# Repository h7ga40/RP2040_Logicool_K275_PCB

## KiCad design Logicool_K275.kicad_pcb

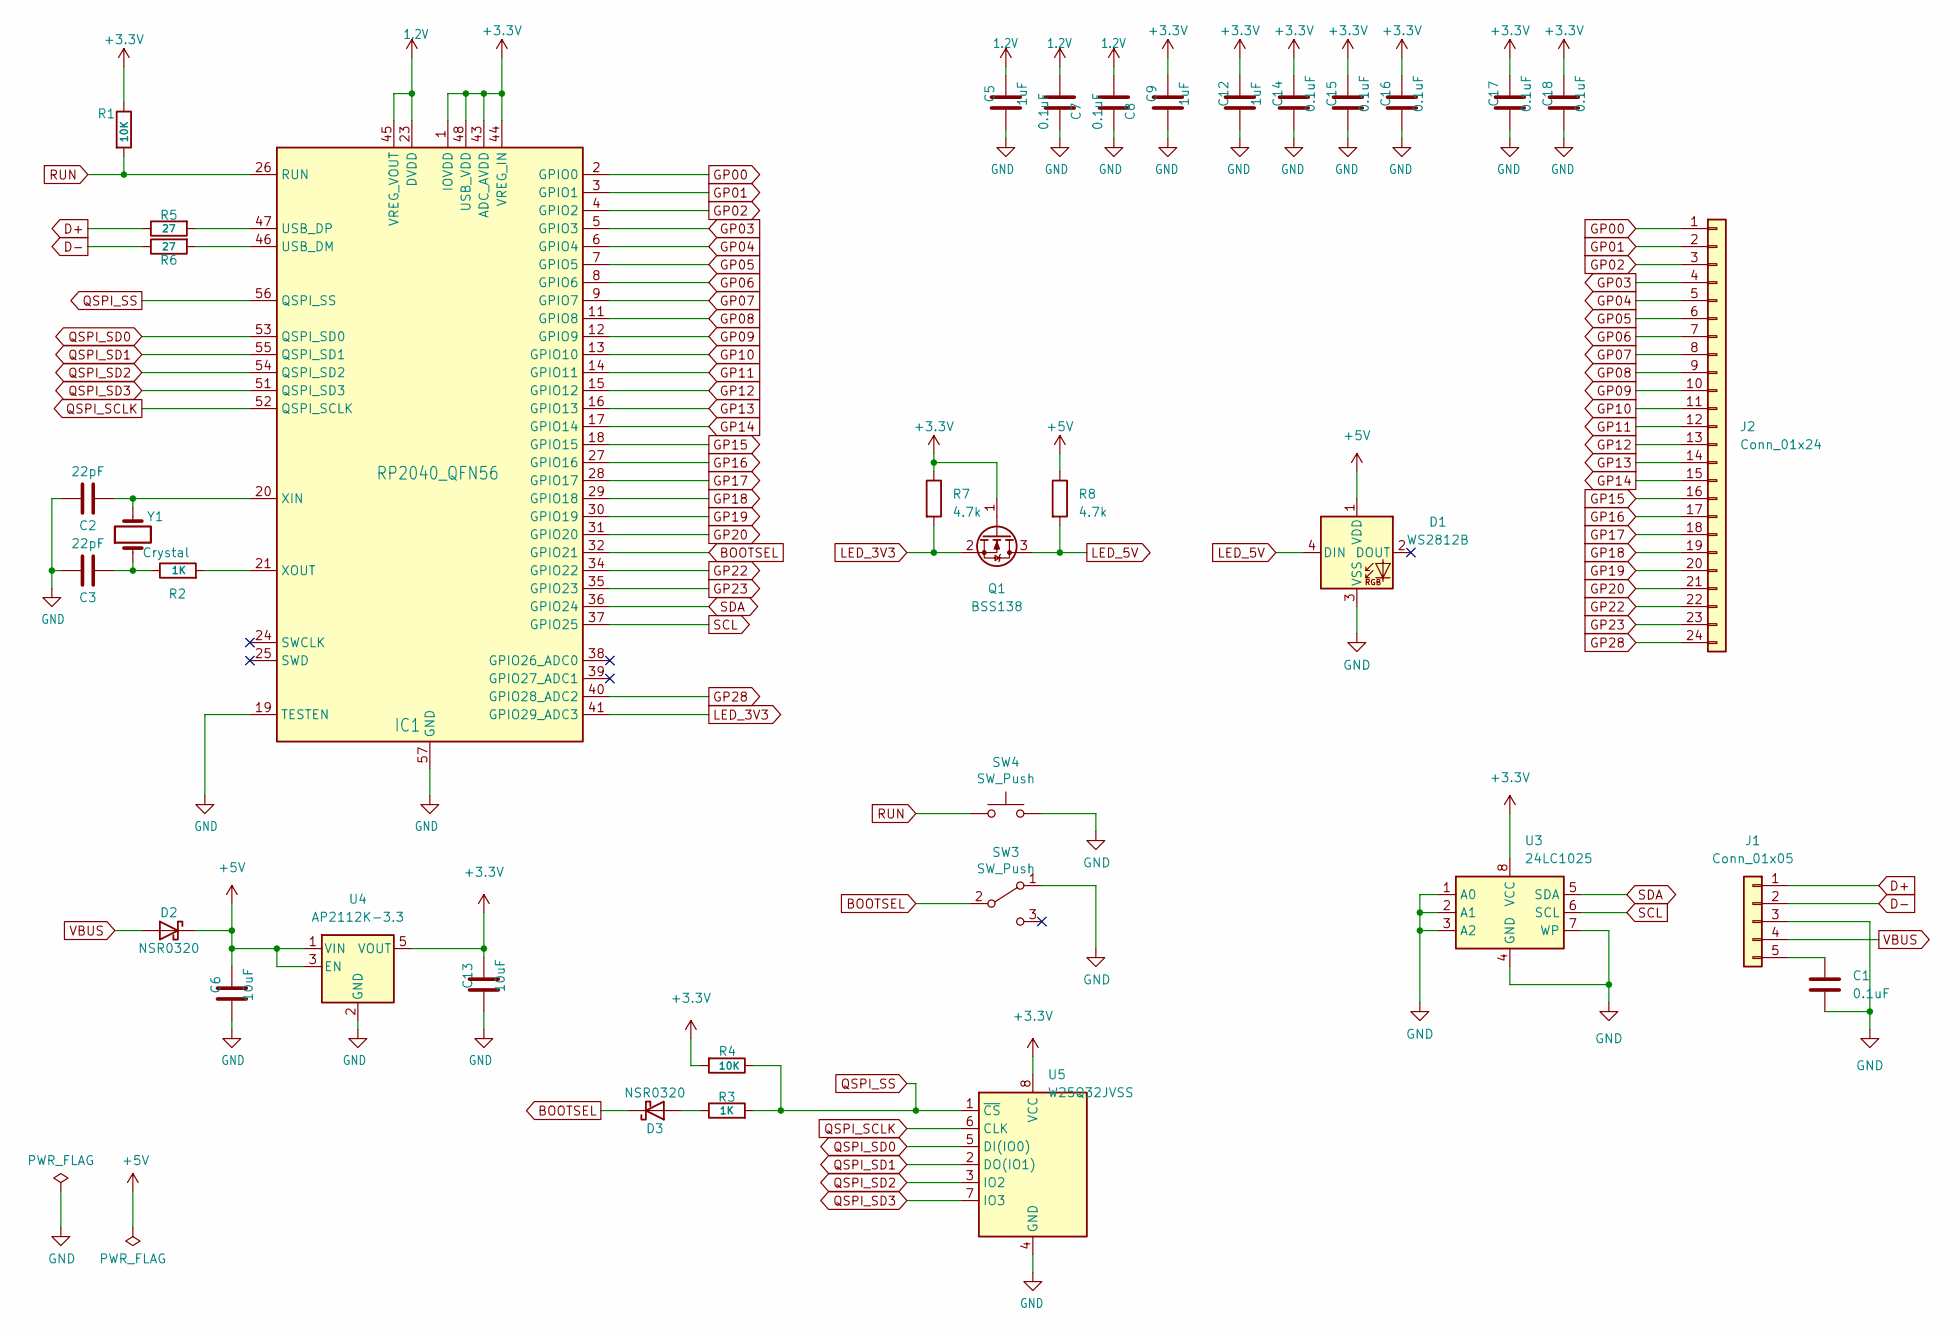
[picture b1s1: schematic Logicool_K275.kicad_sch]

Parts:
C1, C7, C8, C14, C15, C16, C17, C18: 0.1uF; C_0603_1608Metric_Pad1.08x0.95mm_HandSolder
C2, C3: 22pF; C_0603_1608Metric_Pad1.08x0.95mm_HandSolder
C5, C9, C12: 1uF; C_0603_1608Metric_Pad1.08x0.95mm_HandSolder
C6, C13: 10uF; C_0603_1608Metric_Pad1.08x0.95mm_HandSolder
D1: WS2812B; LED_WS2812B_PLCC4_5.0x5.0mm_P3.2mm
D2, D3: NSR0320; D_SOD-323_HandSoldering
IC1: RP2040_QFN56; QFN-56-1EP_7x7mm_P0.4mm_EP3.2x3.2mm
J1: Conn_01x05; PinHeader_1x05_P2.00mm_Vertical
J2: Conn_01x24; KeyMatrix
Q1: BSS138; SOT-23
R1, R4: 10K; R_0603_1608Metric_Pad0.98x0.95mm_HandSolder
R2, R3: 1K; R_0603_1608Metric_Pad0.98x0.95mm_HandSolder
R5, R6: 27; R_0603_1608Metric_Pad0.98x0.95mm_HandSolder
R7, R8: 4.7k; R_0603_1608Metric_Pad0.98x0.95mm_HandSolder
SW3: SW_Push; SW_SPDT_PCM12
SW4: SW_Push; SW_SPST_PTS810
U3: 24LC1025; SOP-8_3.9x4.9mm_P1.27mm
U4: AP2112K-3.3; SOT-23-5
U5: W25Q32JVSS; SOIC-8_5.23x5.23mm_P1.27mm
Y1: Crystal; Crystal_HC49-U_Vertical

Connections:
+1V2: C5.1, C7.2, C8.2, IC1.23 (DVDD), IC1.45 (VREG_VOUT), IC1.50 (DVDD)
+3.3V: C9.1, C12.1, C13.1, C14.1, C15.1, C16.1, C17.1, C18.1, IC1.1 (IOVDD), IC1.10 (IOVDD), IC1.22 (IOVDD), IC1.33 (IOVDD), IC1.42 (IOVDD), IC1.43 (ADC_AVDD), IC1.44 (VREG_IN), IC1.48 (USB_VDD), IC1.49 (IOVDD), Q1.1 (G), R1.1, R4.2, R7.1, U3.8 (VCC), U4.5 (VOUT), U5.8 (VCC)
+5V: C6.1, D1.1 (VDD), D2.1 (K), R8.1, U4.1 (VIN), U4.3 (EN)
BOOTSEL: D3.1 (K), IC1.32 (GPIO21), SW3.2 (B)
D+: J1.1, R5.1
D-: J1.2, R6.1
GND: C1.2, C2.1, C3.1, C5.2, C6.2, C7.1, C8.1, C9.2, C12.2, C13.2, C14.2, C15.2, C16.2, C17.2, C18.2, D1.3 (VSS), IC1.19 (TESTEN), IC1.57 (GND), J1.3, SW3.1 (A), SW4.2, U3.1 (A0), U3.2 (A1), U3.3 (A2), U3.4 (GND), U3.7 (WP), U4.2 (GND), U5.4 (GND)
GP00: IC1.2 (GPIO0), J2.1
GP01: IC1.3 (GPIO1), J2.2
GP02: IC1.4 (GPIO2), J2.3
GP03: IC1.5 (GPIO3), J2.4
GP04: IC1.6 (GPIO4), J2.5
GP05: IC1.7 (GPIO5), J2.6
GP06: IC1.8 (GPIO6), J2.7
GP07: IC1.9 (GPIO7), J2.8
GP08: IC1.11 (GPIO8), J2.9
GP09: IC1.12 (GPIO9), J2.10
GP10: IC1.13 (GPIO10), J2.11
GP11: IC1.14 (GPIO11), J2.12
GP12: IC1.15 (GPIO12), J2.13
GP13: IC1.16 (GPIO13), J2.14
GP14: IC1.17 (GPIO14), J2.15
GP15: IC1.18 (GPIO15), J2.16
GP16: IC1.27 (GPIO16), J2.17
GP17: IC1.28 (GPIO17), J2.18
GP18: IC1.29 (GPIO18), J2.19
GP19: IC1.30 (GPIO19), J2.20
GP20: IC1.31 (GPIO20), J2.21
GP22: IC1.34 (GPIO22), J2.22
GP23: IC1.35 (GPIO23), J2.23
GP28: IC1.40 (GPIO28_ADC2), J2.24
LED_3V3: IC1.41 (GPIO29_ADC3), Q1.2 (S), R7.2
LED_5V: D1.4 (DIN), Q1.3 (D), R8.2
unnamed: C3.2, R2.1, Y1.1
unnamed: D3.2 (A), R3.1
unnamed: IC1.46 (USB_DM), R6.2
unnamed: IC1.47 (USB_DP), R5.2
unnamed: C2.2, IC1.20 (XIN), Y1.2
unnamed: IC1.21 (XOUT), R2.2
unnamed: C1.1, J1.5
QSPI_SCLK: IC1.52 (QSPI_SCLK), U5.6 (CLK)
QSPI_SD0: IC1.53 (QSPI_SD0), U5.5 (DI(IO0))
QSPI_SD1: IC1.55 (QSPI_SD1), U5.2 (DO(IO1))
QSPI_SD2: IC1.54 (QSPI_SD2), U5.3 (IO2)
QSPI_SD3: IC1.51 (QSPI_SD3), U5.7 (IO3)
QSPI_SS: IC1.56 (QSPI_SS), R3.2, R4.1, U5.1 (~CS)
RUN: IC1.26 (RUN), R1.2, SW4.1
SCL: IC1.37 (GPIO25), U3.6 (SCL)
SDA: IC1.36 (GPIO24), U3.5 (SDA)
VBUS: D2.2 (A), J1.4

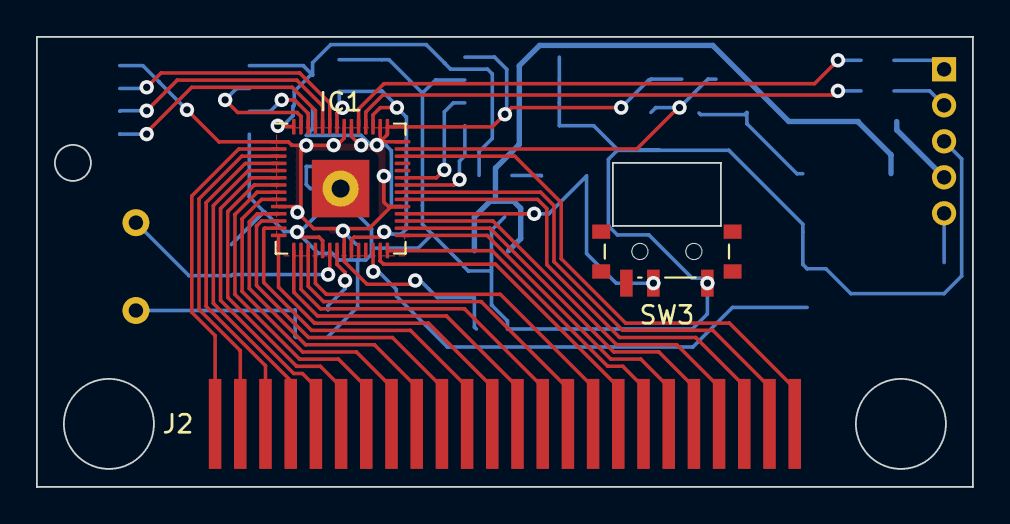
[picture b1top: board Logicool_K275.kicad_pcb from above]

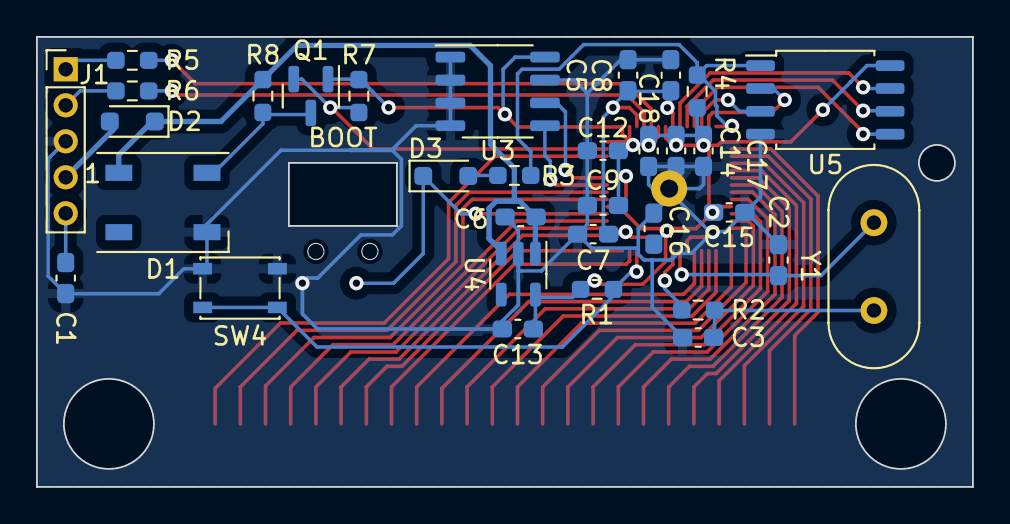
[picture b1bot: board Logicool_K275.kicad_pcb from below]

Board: 2 copper layers, 52.0 x 25.0 mm, 36 parts (33 on the bottom side), 50 nets.

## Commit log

2023-06-18 ファイルを登録
2023-06-18 QMK firmwareのコードを追加
2023-10-14 Neopixelの信号線にレベル変換を追加
